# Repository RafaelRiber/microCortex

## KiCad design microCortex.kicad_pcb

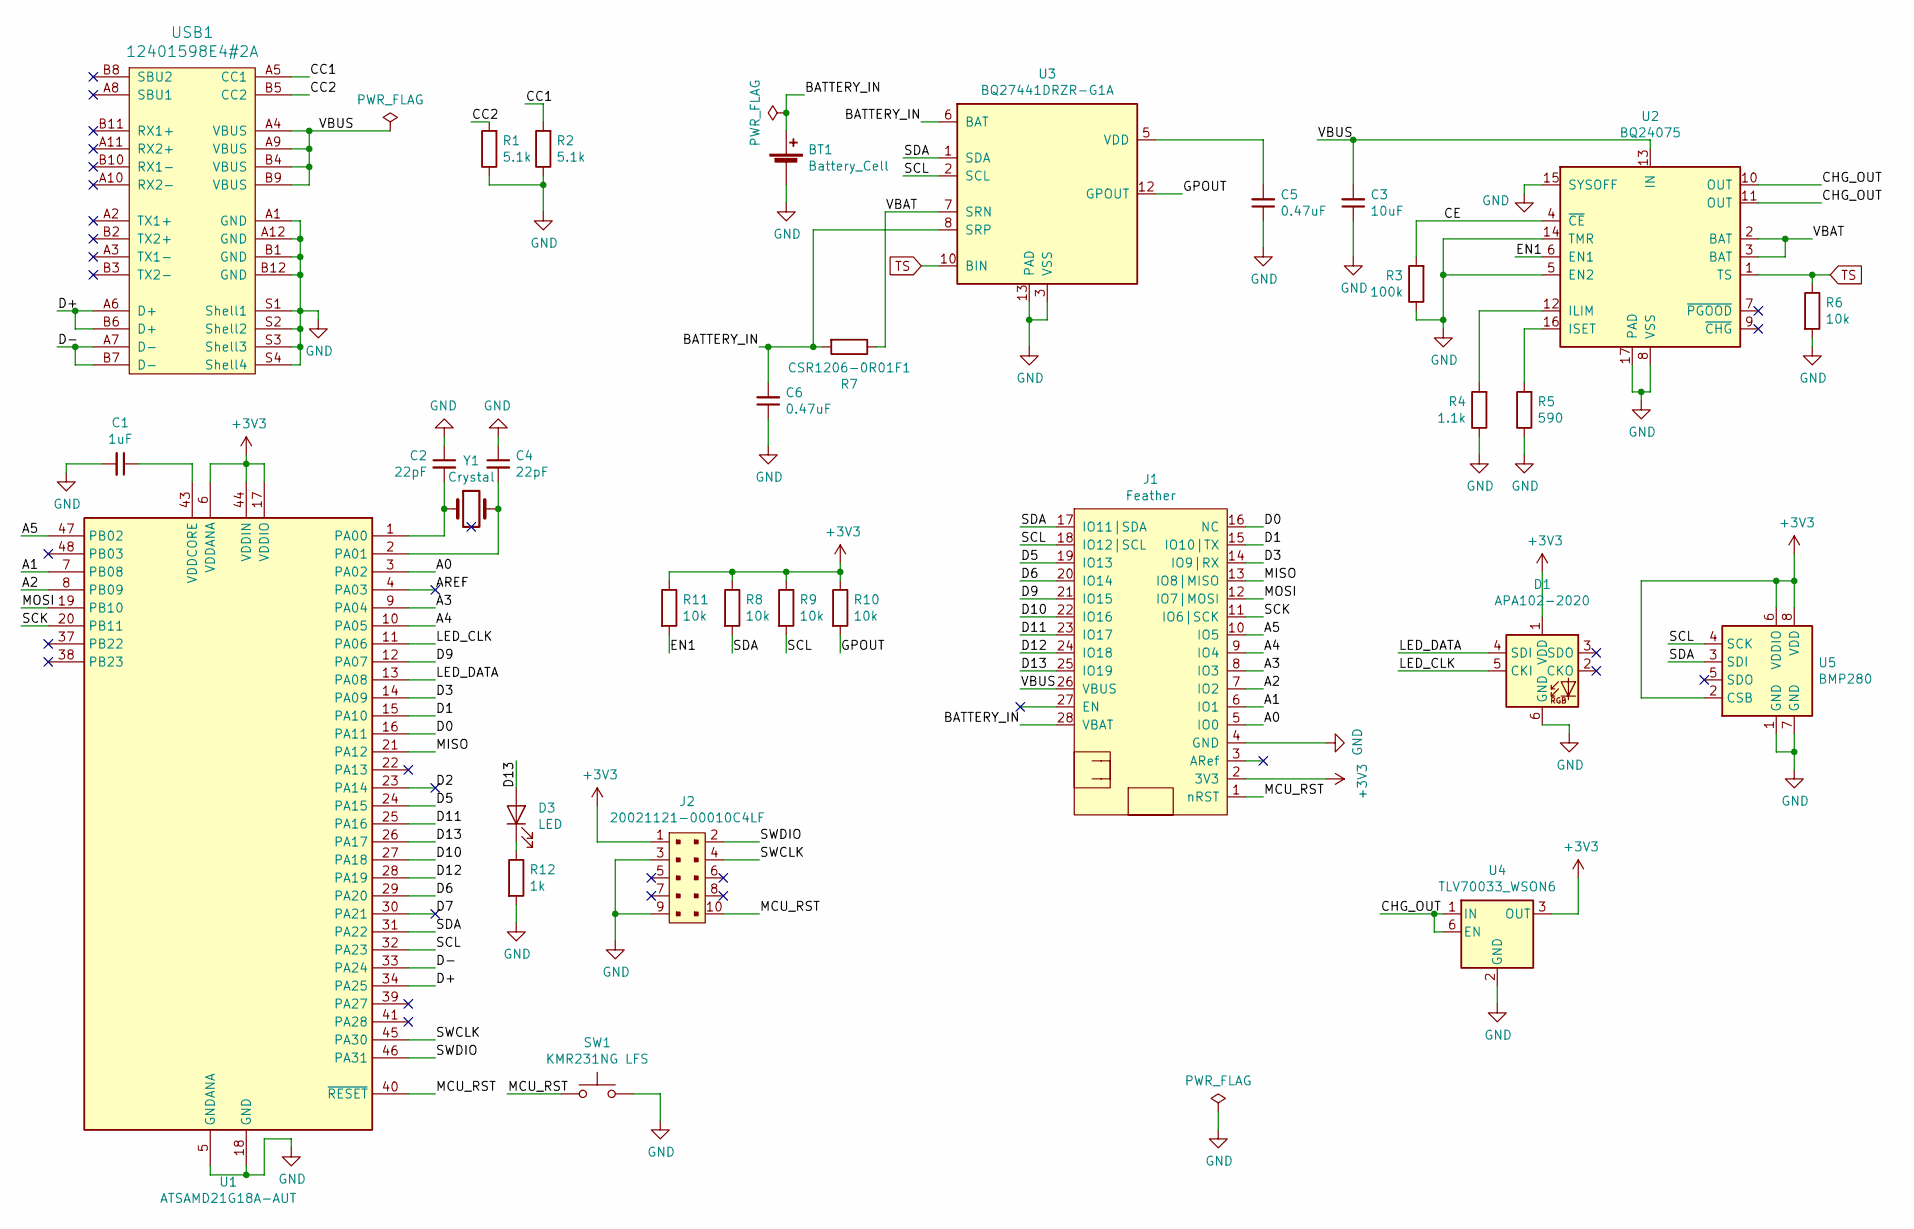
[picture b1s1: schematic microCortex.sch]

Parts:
BT1: Battery_Cell; JST_PH_S2B-PH-SM4-TB_1x02-1MP_P2.00mm_Horizontal
C1: 1uF; C_0402_1005Metric
C2, C4: 22pF; C_0402_1005Metric
C3: 10uF; C_0402_1005Metric
C5, C6: 0.47uF; C_0402_1005Metric
D1: APA102-2020; LED-APA102-2020
D3: LED; LED_0805_2012Metric
J1: Feather; featherwing
J2: 20021121-00010C4LF; PinHeader_2x5_P1.27mm; MPN 20021121-00010C4LF; Digi-Key_PN 609-3695-1-ND
R1, R2: 5.1k; R_0402_1005Metric
R3: 100k; R_0402_1005Metric
R4: 1.1k; R_0402_1005Metric
R5: 590; R_0402_1005Metric
R6, R8, R9, R10, R11: 10k; R_0402_1005Metric
R7: CSR1206-0R01F1; R_1206_3216Metric
R12: 1k; R_0402_1005Metric
SW1: KMR231NG LFS; SW_Push_1P1T_NO_CK_KMR2
U1: ATSAMD21G18A-AUT; QFN50P700X700X90-49N
U2: BQ24075; QFN-16-1EP_3x3mm_P0.5mm_EP1.75x1.75mm_ThermalVias
U3: BQ27441DRZR-G1A; Texas_S-PDSO-N12
U4: TLV70033_WSON6; WSON-6_1.5x1.5mm_P0.5mm
U5: BMP280; Bosch_LGA-8_2x2.5mm_P0.65mm_ClockwisePinNumbering
USB1: 12401598E4#2A
Y1: Crystal; Crystal_SMD_3215-2Pin_3.2x1.5mm

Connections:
+3V3: D1.1 (VDD), J1.2 (3V3), J2.1, R8.1, R9.1, R10.1, R11.1, U1.6 (VDDANA), U1.17 (VDDIO), U1.36 (VDDIO), U1.44 (VDDIN), U4.3 (OUT), U5.2 (CSB), U5.6 (VDDIO), U5.8 (VDD)
/A0: J1.5 (IO0), U1.3 (PA02)
/A1: J1.6 (IO1), U1.7 (PB08)
/A2: J1.7 (IO2), U1.8 (PB09)
/A3: J1.8 (IO3), U1.9 (PA04)
/A4: J1.9 (IO4), U1.10 (PA05)
/A5: J1.10 (IO5), U1.47 (PB02)
/AREF: U1.4 (PA03)
/BATTERY_IN: BT1.1 (+), C6.2, J1.28 (VBAT), R7.2, U3.6 (BAT), U3.8 (SRP)
/CC1: R2.2, USB1.A5 (CC1)
/CC2: R1.2, USB1.B5 (CC2)
/CE: R3.2, U2.4 (~CE)
/CHG_OUT: U2.10 (OUT), U2.11 (OUT), U4.1 (IN), U4.6 (EN)
/D0: J1.16 (NC), U1.16 (PA11)
/D1: J1.15 (IO10|TX), U1.15 (PA10)
/D2: U1.23 (PA14)
/D3: J1.14 (IO9|RX), U1.14 (PA09)
/D5: J1.19 (IO13), U1.24 (PA15)
/D6: J1.20 (IO14), U1.29 (PA20)
/D7: U1.30 (PA21)
/D9: J1.21 (IO15), U1.12 (PA07)
/D10: J1.22 (IO16), U1.27 (PA18)
/D11: J1.23 (IO17), U1.25 (PA16)
/D12: J1.24 (IO18), U1.28 (PA19)
/D13: D3.2 (A), J1.25 (IO19), U1.26 (PA17)
/D+: U1.34 (PA25), USB1.A6 (D+), USB1.B6 (D+)
/D-: U1.33 (PA24), USB1.A7 (D-), USB1.B7 (D-)
/EN1: R11.2, U2.6 (EN1)
/GPOUT: R10.2, U3.12 (GPOUT)
/LED_CLK: D1.5 (CKI), U1.11 (PA06)
/LED_DATA: D1.4 (SDI), U1.13 (PA08)
/MCU_RST: J1.1 (nRST), J2.10, SW1.1, U1.40 (~RESET)
/MISO: J1.13 (IO8|MISO), U1.21 (PA12)
/MOSI: J1.12 (IO7|MOSI), U1.19 (PB10)
/SCK: J1.11 (IO6|SCK), U1.20 (PB11)
/SCL: J1.18 (IO12|SCL), R9.2, U1.32 (PA23), U3.2 (SCL), U5.4 (SCK)
/SDA: J1.17 (IO11|SDA), R8.2, U1.31 (PA22), U3.1 (SDA), U5.3 (SDI)
/SWCLK: J2.4, U1.45 (PA30)
/SWDIO: J2.2, U1.46 (PA31)
/VBAT: R7.1, U2.2 (BAT), U2.3 (BAT), U3.7 (SRN)
/VBUS: C3.2, J1.26 (VBUS), U2.13 (IN), USB1.A4 (VBUS), USB1.A9 (VBUS), USB1.B4 (VBUS), USB1.B9 (VBUS)
GND: BT1.2 (-), C1.2, C2.1, C3.1, C4.1, C5.1, C6.1, D1.6 (GND), J1.4 (GND), J2.3, J2.9, R1.1, R2.1, R3.1, R4.1, R5.1, R6.2, R12.2, SW1.2, U1.5 (GNDANA), U1.18 (GND), U1.35 (GND), U1.42 (GND), U2.5 (EN2), U2.8 (VSS), U2.14 (TMR), U2.15 (SYSOFF), U2.17 (PAD), U3.3 (VSS), U3.13 (PAD), U4.2 (GND), U5.1 (GND), U5.7 (GND), USB1.A1 (GND), USB1.A12 (GND), USB1.B1 (GND), USB1.B12 (GND), USB1.S1 (Shell1), USB1.S2 (Shell2), USB1.S3 (Shell3), USB1.S4 (Shell4)
unnamed: C1.1, U1.43 (VDDCORE)
unnamed: C2.2, U1.1 (PA00), Y1.1
unnamed: C4.2, U1.2 (PA01), Y1.2
unnamed: C5.2, U3.5 (VDD)
unnamed: D3.1 (K), R12.1
unnamed: R4.2, U2.12 (ILIM)
unnamed: R5.2, U2.16 (ISET)
TS: R6.1, U2.1 (TS), U3.10 (BIN)

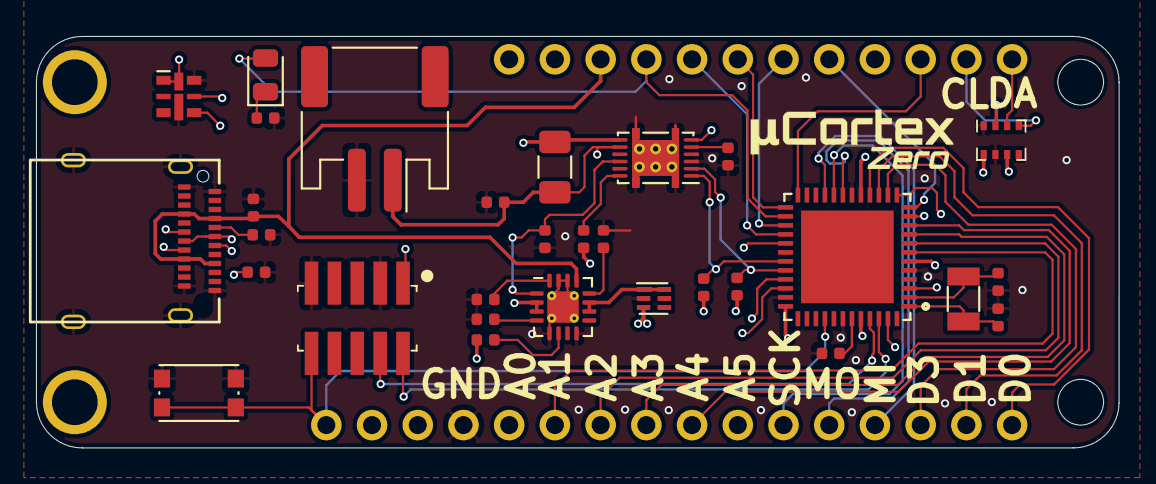
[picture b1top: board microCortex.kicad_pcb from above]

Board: 4 copper layers, 60.1 x 22.9 mm, 31 parts (0 on the bottom side), 47 nets.

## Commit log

2019-12-18 Added logo
2019-12-18 update gitignore
2019-12-18 Updated pcb
2019-12-18 Updated BMP280 3D model
2019-12-18 Wierd bug
2019-12-19 update ignore
2019-12-19 Upload PDF & add pin numbers
